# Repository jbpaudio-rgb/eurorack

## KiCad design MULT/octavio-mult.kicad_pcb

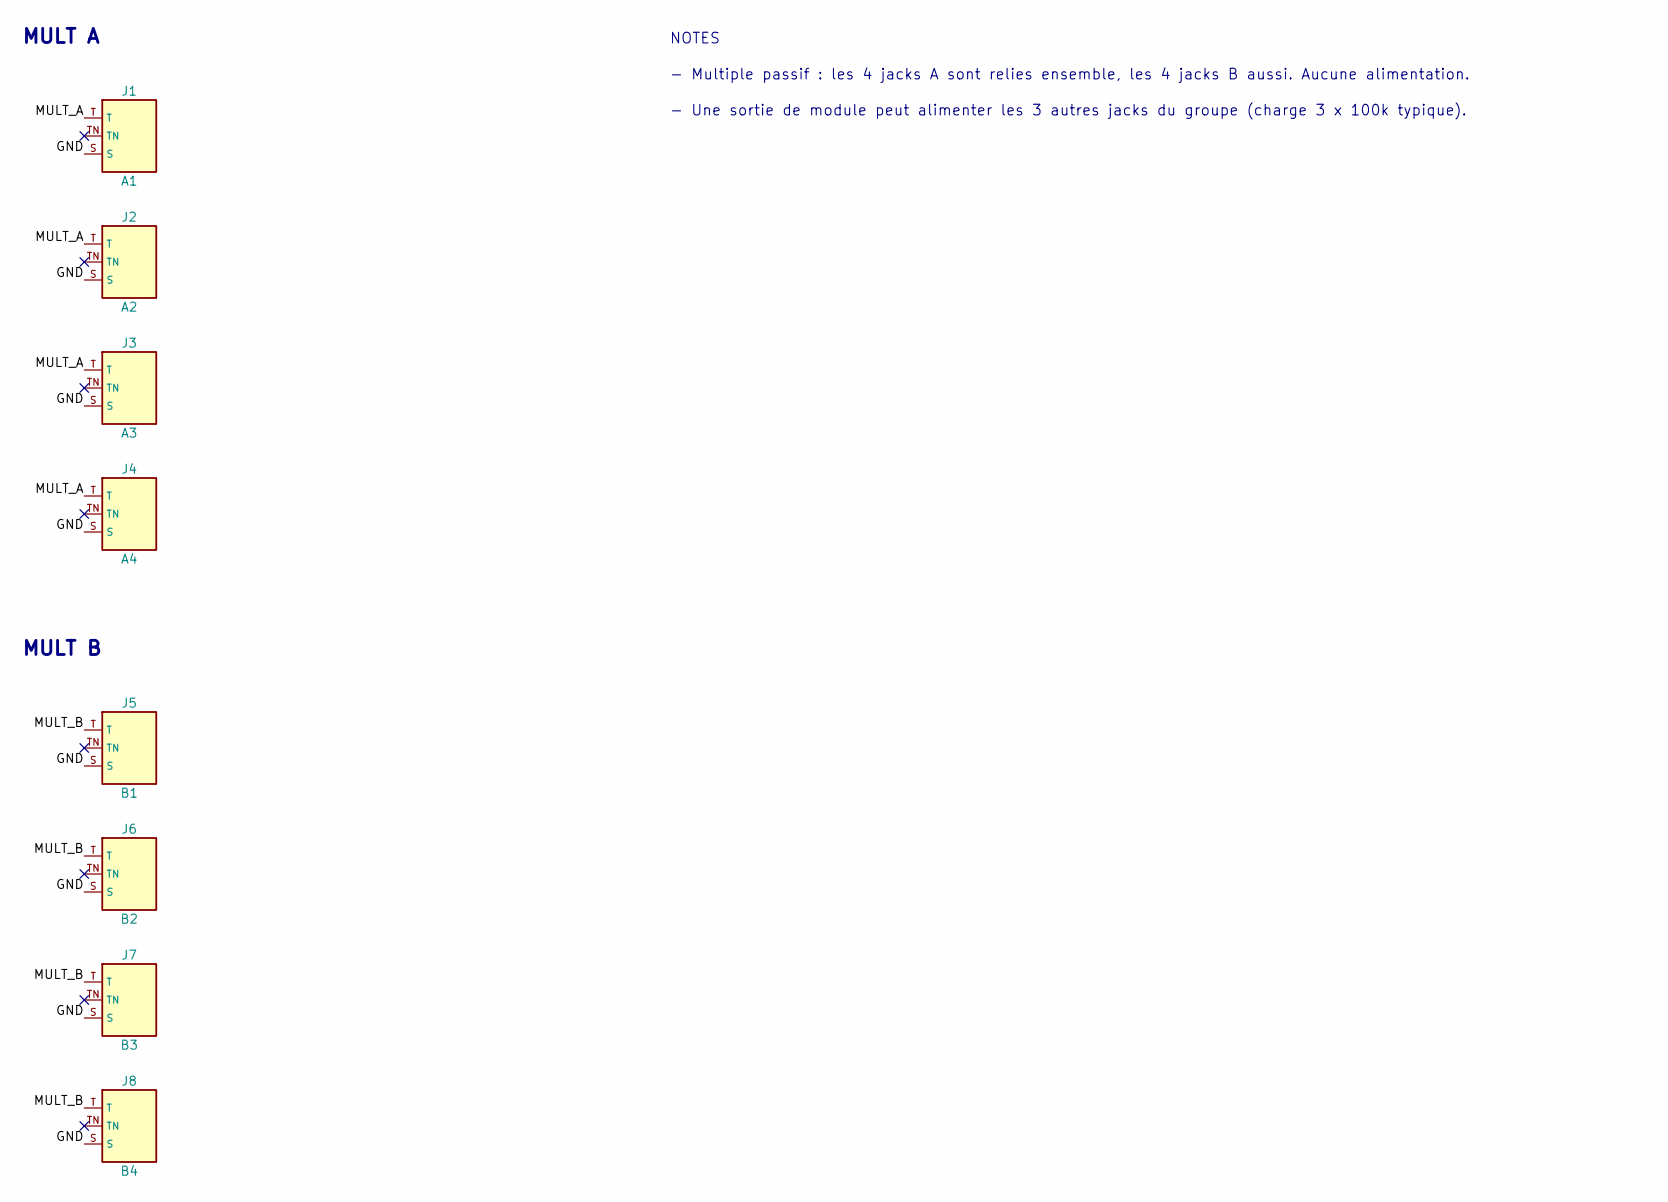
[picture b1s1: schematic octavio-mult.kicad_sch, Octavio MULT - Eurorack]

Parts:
J1: A1; Jack_3.5mm_Thonkiconn_PJ398SM; MPN QingPu WQP-PJ301M-12 (Thonkiconn)
J2: A2; Jack_3.5mm_Thonkiconn_PJ398SM; MPN QingPu WQP-PJ301M-12 (Thonkiconn)
J3: A3; Jack_3.5mm_Thonkiconn_PJ398SM; MPN QingPu WQP-PJ301M-12 (Thonkiconn)
J4: A4; Jack_3.5mm_Thonkiconn_PJ398SM; MPN QingPu WQP-PJ301M-12 (Thonkiconn)
J5: B1; Jack_3.5mm_Thonkiconn_PJ398SM; MPN QingPu WQP-PJ301M-12 (Thonkiconn)
J6: B2; Jack_3.5mm_Thonkiconn_PJ398SM; MPN QingPu WQP-PJ301M-12 (Thonkiconn)
J7: B3; Jack_3.5mm_Thonkiconn_PJ398SM; MPN QingPu WQP-PJ301M-12 (Thonkiconn)
J8: B4; Jack_3.5mm_Thonkiconn_PJ398SM; MPN QingPu WQP-PJ301M-12 (Thonkiconn)

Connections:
GND: J1.S, J2.S, J3.S, J4.S, J5.S, J6.S, J7.S, J8.S
MULT_A: J1.T, J2.T, J3.T, J4.T
MULT_B: J5.T, J6.T, J7.T, J8.T

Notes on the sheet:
MULT A
MULT B
NOTES
- Multiple passif : les 4 jacks A sont relies ensemble, les 4 jacks B aussi. Aucune alimentation.
- Une sortie de module peut alimenter les 3 autres jacks du groupe (charge 3 x 100k typique).

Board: 2 copper layers, 8 parts (0 on the bottom side), 3 nets, no tracks yet.

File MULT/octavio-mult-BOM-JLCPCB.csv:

Comment,Designator,Footprint,LCSC Part #,Notes
A1,J1,Jack_3.5mm_Thonkiconn_PJ398SM,C9900080080,QingPu WQP-PJ301M-12 (Thonkiconn) - THT (wave soldering)
A2,J2,Jack_3.5mm_Thonkiconn_PJ398SM,C9900080080,QingPu WQP-PJ301M-12 (Thonkiconn) - THT (wave soldering)
A3,J3,Jack_3.5mm_Thonkiconn_PJ398SM,C9900080080,QingPu WQP-PJ301M-12 (Thonkiconn) - THT (wave soldering)
A4,J4,Jack_3.5mm_Thonkiconn_PJ398SM,C9900080080,QingPu WQP-PJ301M-12 (Thonkiconn) - THT (wave soldering)
B1,J5,Jack_3.5mm_Thonkiconn_PJ398SM,C9900080080,QingPu WQP-PJ301M-12 (Thonkiconn) - THT (wave soldering)
B2,J6,Jack_3.5mm_Thonkiconn_PJ398SM,C9900080080,QingPu WQP-PJ301M-12 (Thonkiconn) - THT (wave soldering)
B3,J7,Jack_3.5mm_Thonkiconn_PJ398SM,C9900080080,QingPu WQP-PJ301M-12 (Thonkiconn) - THT (wave soldering)
B4,J8,Jack_3.5mm_Thonkiconn_PJ398SM,C9900080080,QingPu WQP-PJ301M-12 (Thonkiconn) - THT (wave soldering)

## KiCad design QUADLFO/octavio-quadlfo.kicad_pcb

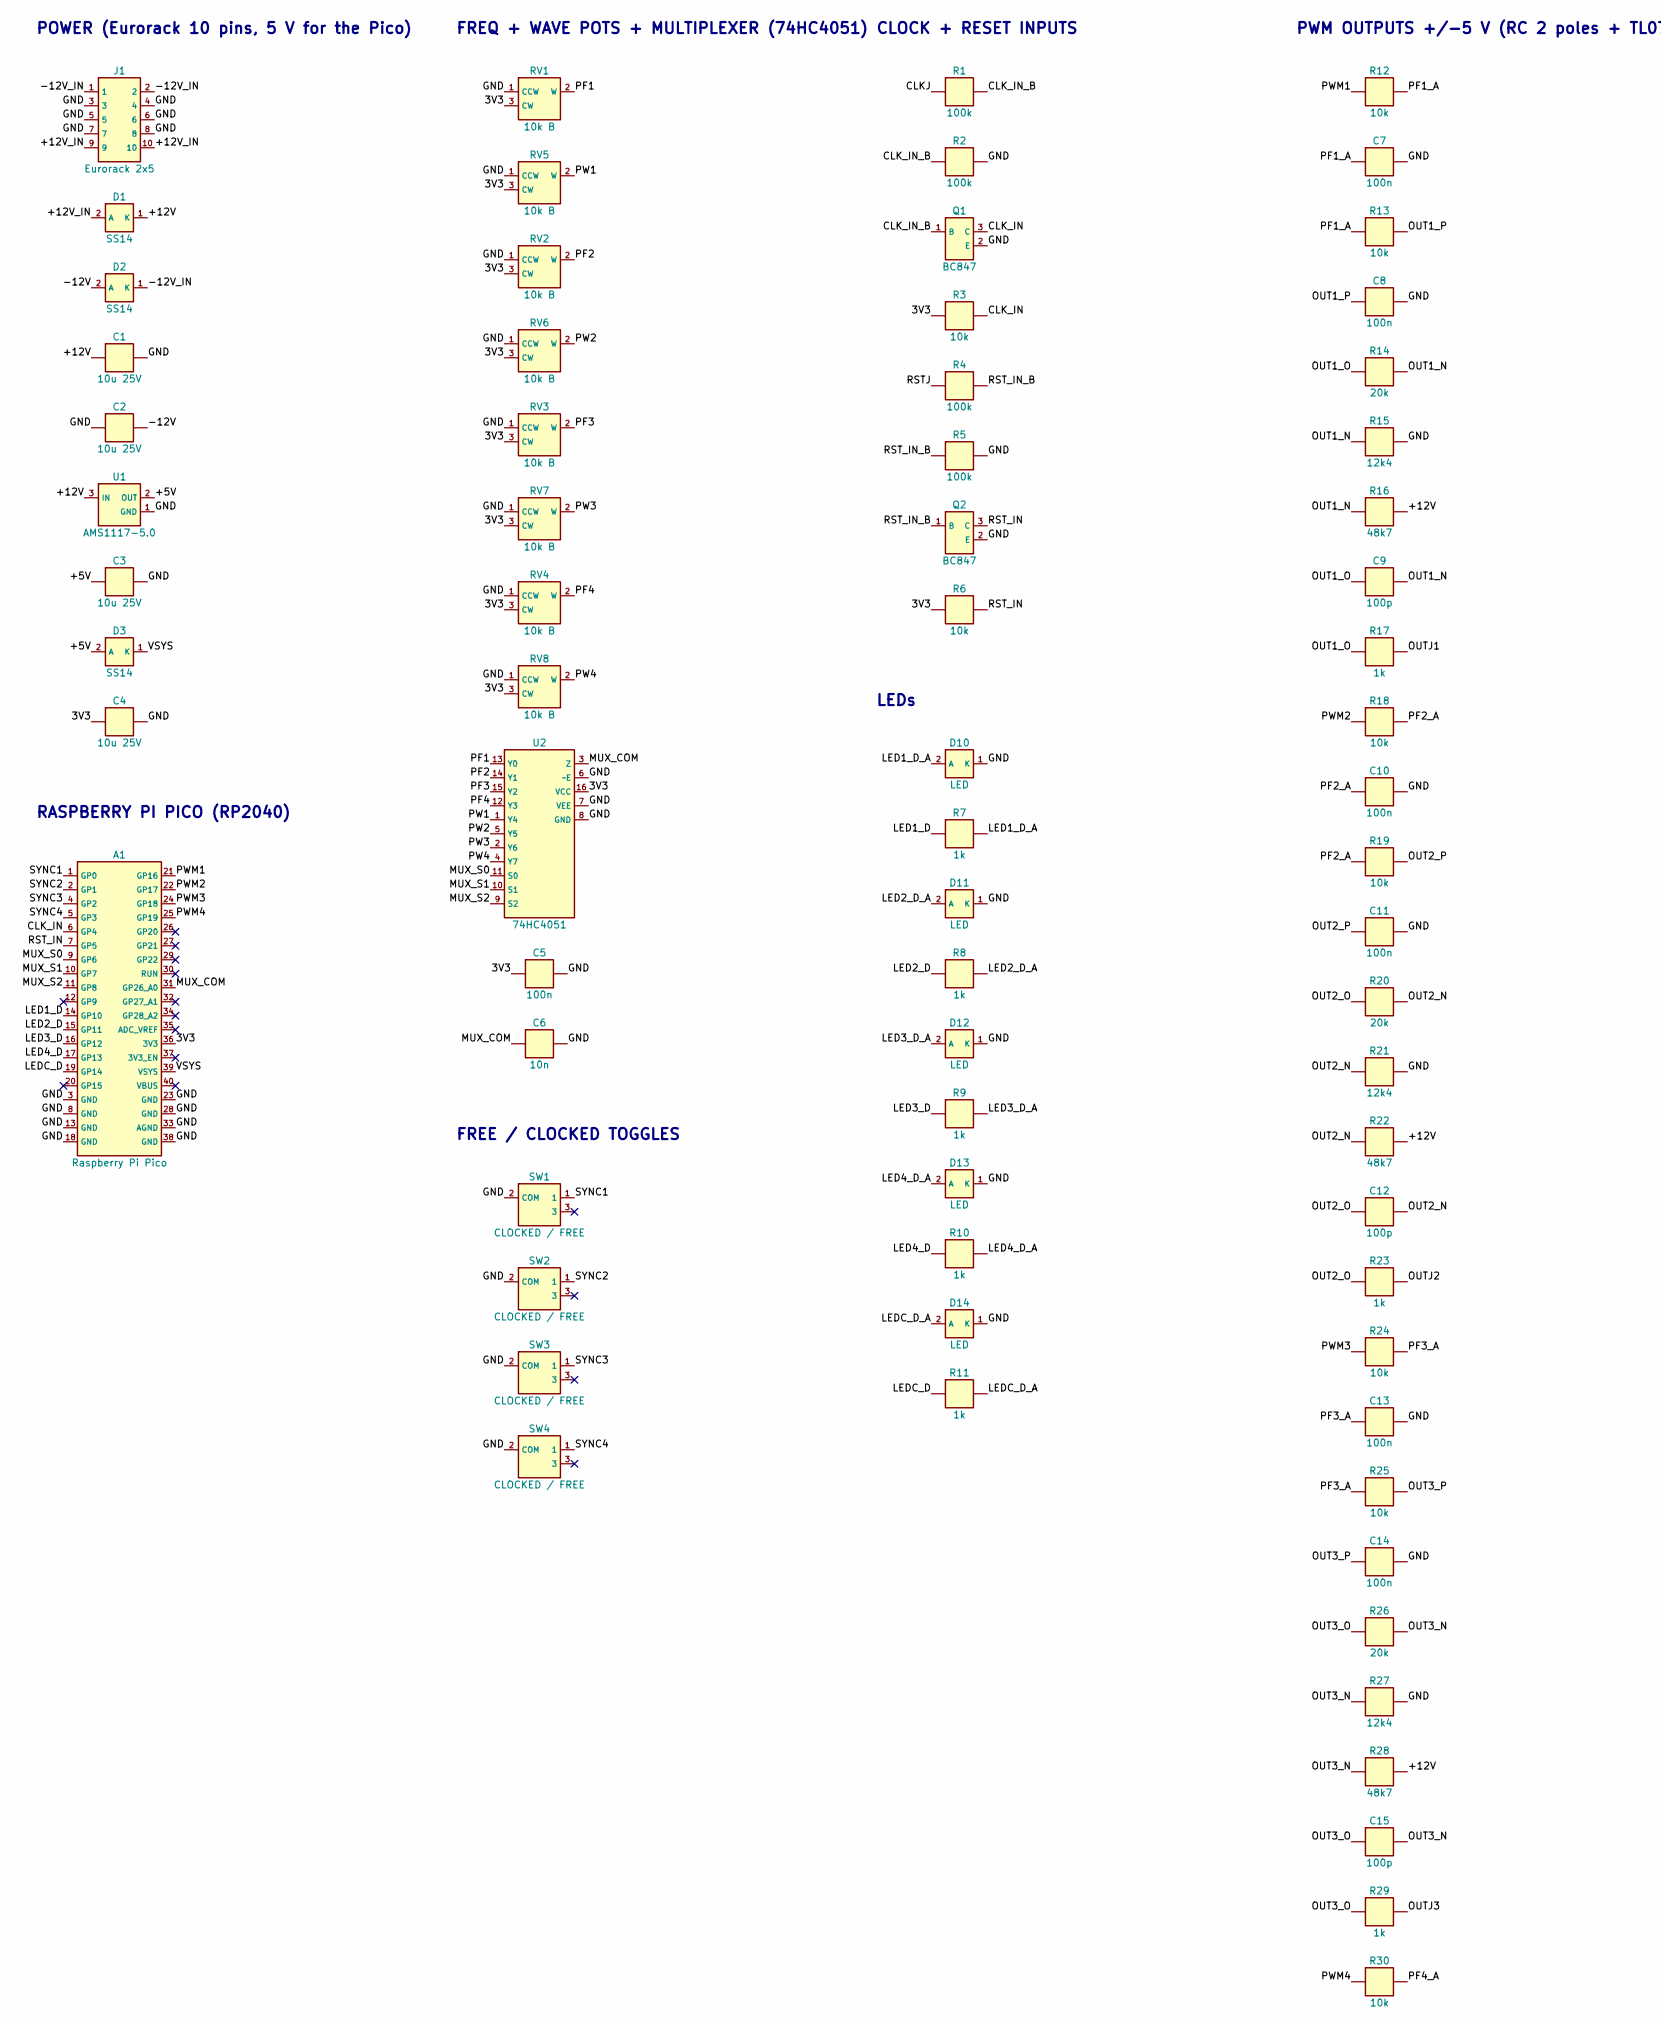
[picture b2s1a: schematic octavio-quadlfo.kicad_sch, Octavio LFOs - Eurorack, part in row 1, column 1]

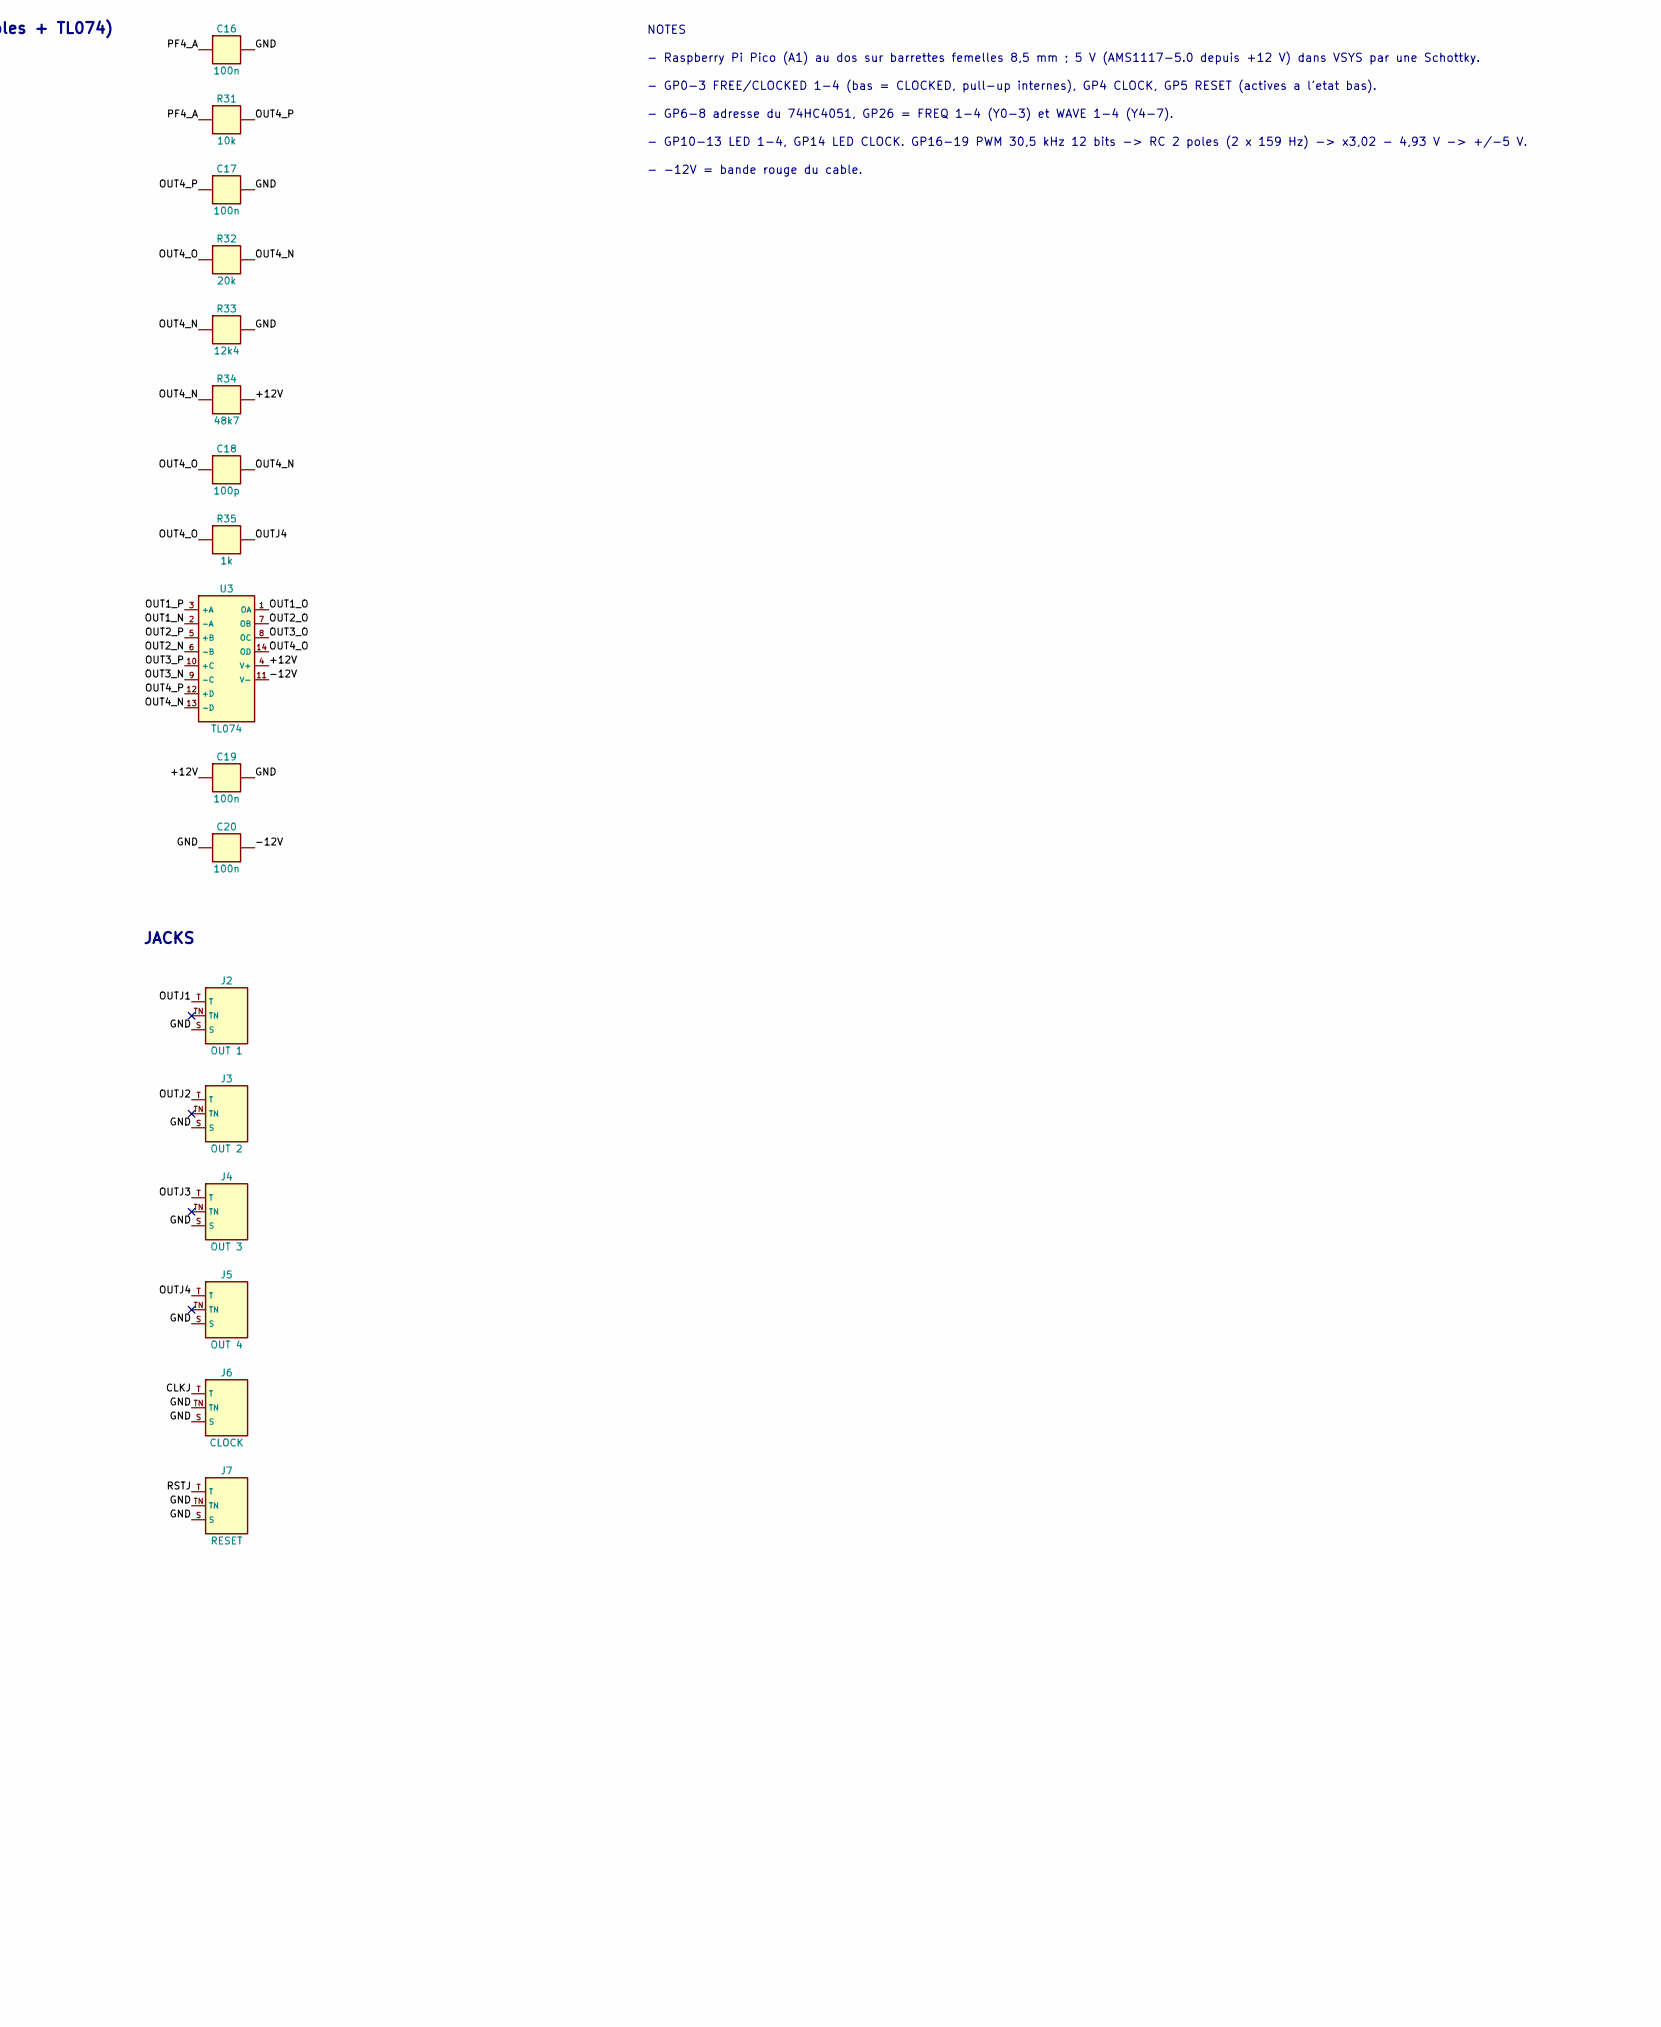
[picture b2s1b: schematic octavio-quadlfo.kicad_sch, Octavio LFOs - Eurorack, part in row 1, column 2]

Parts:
A1: Raspberry Pi Pico; RaspberryPi_Pico_Headers; MPN Raspberry Pi Pico (RP2040) sur 2 barret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
C1, C2, C3: 10u 25V; C_1206_3216Metric; MPN X5R/X7R 1206
C4: 10u 25V; C_1206_3216Metric; MPN X5R/X7R 1206 (3,3 V des potentiomètres 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
C5, C7, C8, C10, C11, C13, C14, C16, C17, C19, C20: 100n; C_0603_1608Metric
C6: 10n; C_0603_1608Metric
C9, C12, C15, C18: 100p; C_0603_1608Metric
D1, D2: SS14; D_SMA; MPN SS14 (40 V 1 A Schottky)
D3: SS14; D_SMA; MPN SS14 (Schottky : USB et rack peuvent êt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
D10, D11, D12, D13: LED; LED_D3.0mm; MPN LED 3 mm rouge (suit le LFO, PWM)
D14: LED; LED_D3.0mm; MPN LED 3 mm ambre (CLOCK)
J1: Eurorack 2x5; IDC-Header_2x05_P2.54mm_Vertical; MPN Shrouded header 2x5 2.54 mm
J2: OUT 1; Jack_3.5mm_Thonkiconn_PJ398SM; MPN QingPu WQP-PJ301M-12 (Thonkiconn)
J3: OUT 2; Jack_3.5mm_Thonkiconn_PJ398SM; MPN QingPu WQP-PJ301M-12 (Thonkiconn)
J4: OUT 3; Jack_3.5mm_Thonkiconn_PJ398SM; MPN QingPu WQP-PJ301M-12 (Thonkiconn)
J5: OUT 4; Jack_3.5mm_Thonkiconn_PJ398SM; MPN QingPu WQP-PJ301M-12 (Thonkiconn)
J6: CLOCK; Jack_3.5mm_Thonkiconn_PJ398SM; MPN QingPu WQP-PJ301M-12 (Thonkiconn)
J7: RESET; Jack_3.5mm_Thonkiconn_PJ398SM; MPN QingPu WQP-PJ301M-12 (Thonkiconn)
Q1, Q2: BC847; SOT-23; MPN BC847C
R1, R2, R4, R5: 100k; R_0603_1608Metric
R3, R6, R12, R13, R18, R19, R24, R25, R30, R31: 10k; R_0603_1608Metric
R7, R8, R9, R10, R11, R17, R23, R29, R35: 1k; R_0603_1608Metric
R14, R20, R26, R32: 20k; R_0603_1608Metric
R15, R21, R27, R33: 12k4; R_0603_1608Metric
R16, R22, R28, R34: 48k7; R_0603_1608Metric
RV1, RV2, RV3, RV4, RV5, RV6, RV7, RV8: 10k B; Pot_Alpha_9mm_Vertical; MPN POT-R09V-10K (9 mm vertical, B10k)
SW1, SW2, SW3, SW4: CLOCKED / FREE; Toggle_SPDT_Dailywell_2MS1; MPN Dailywell 2MS1T1B1M2QES (SPDT ON-ON, le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
U1: AMS1117-5.0; SOT-223-3_TabPin2; MPN AMS1117-5.0 (C6187)
U2: 74HC4051; SOIC-16_3.9x9.9mm_P1.27mm; MPN 74HC4051D
U3: TL074; SOIC-14_3.9x8.7mm_P1.27mm; MPN TL074CDR

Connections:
3V3: A1.36 (3V3), C4.1, C5.1, R3.1, R6.1, RV1.3 (CW), RV2.3 (CW), RV3.3 (CW), RV4.3 (CW), RV5.3 (CW), RV6.3 (CW), RV7.3 (CW), RV8.3 (CW), U2.16 (VCC)
+5V: C3.1, D3.2 (A), U1.2 (OUT)
+12V: C1.1, C19.1, D1.1 (K), R16.2, R22.2, R28.2, R34.2, U1.3 (IN), U3.4 (V+)
+12V_IN: D1.2 (A), J1.9, J1.10
-12V: C2.2, C20.2, D2.2 (A), U3.11 (V-)
-12V_IN: D2.1 (K), J1.1, J1.2
CLKJ: J6.T, R1.1
CLK_IN: A1.6 (GP4), Q1.3 (C), R3.2
CLK_IN_B: Q1.1 (B), R1.2, R2.1
GND: A1.3 (GND), A1.8 (GND), A1.13 (GND), A1.18 (GND), A1.23 (GND), A1.28 (GND), A1.33 (AGND), A1.38 (GND), C1.2, C2.1, C3.2, C4.2, C5.2, C6.2, C7.2, C8.2, C10.2, C11.2, C13.2, C14.2, C16.2, C17.2, C19.2, C20.1, D10.1 (K), D11.1 (K), D12.1 (K), D13.1 (K), D14.1 (K), J1.3, J1.4, J1.5, J1.6, J1.7, J1.8, J2.S, J3.S, J4.S, J5.S, J6.S, J6.TN, J7.S, J7.TN, Q1.2 (E), Q2.2 (E), R2.2, R5.2, R15.2, R21.2, R27.2, R33.2, RV1.1 (CCW), RV2.1 (CCW), RV3.1 (CCW), RV4.1 (CCW), RV5.1 (CCW), RV6.1 (CCW), RV7.1 (CCW), RV8.1 (CCW), SW1.2 (COM), SW2.2 (COM), SW3.2 (COM), SW4.2 (COM), U1.1 (GND), U2.6 (~E), U2.7 (VEE), U2.8 (GND)
LED1_D: A1.14 (GP10), R7.1
LED1_D_A: D10.2 (A), R7.2
LED2_D: A1.15 (GP11), R8.1
LED2_D_A: D11.2 (A), R8.2
LED3_D: A1.16 (GP12), R9.1
LED3_D_A: D12.2 (A), R9.2
LED4_D: A1.17 (GP13), R10.1
LED4_D_A: D13.2 (A), R10.2
LEDC_D: A1.19 (GP14), R11.1
LEDC_D_A: D14.2 (A), R11.2
MUX_COM: A1.31 (GP26_A0), C6.1, U2.3 (Z)
MUX_S0: A1.9 (GP6), U2.11 (S0)
MUX_S1: A1.10 (GP7), U2.10 (S1)
MUX_S2: A1.11 (GP8), U2.9 (S2)
OUT1_N: C9.2, R14.2, R15.1, R16.1, U3.2 (-A)
OUT1_O: C9.1, R14.1, R17.1, U3.1 (OA)
OUT1_P: C8.1, R13.2, U3.3 (+A)
OUT2_N: C12.2, R20.2, R21.1, R22.1, U3.6 (-B)
OUT2_O: C12.1, R20.1, R23.1, U3.7 (OB)
OUT2_P: C11.1, R19.2, U3.5 (+B)
OUT3_N: C15.2, R26.2, R27.1, R28.1, U3.9 (-C)
OUT3_O: C15.1, R26.1, R29.1, U3.8 (OC)
OUT3_P: C14.1, R25.2, U3.10 (+C)
OUT4_N: C18.2, R32.2, R33.1, R34.1, U3.13 (-D)
OUT4_O: C18.1, R32.1, R35.1, U3.14 (OD)
OUT4_P: C17.1, R31.2, U3.12 (+D)
OUTJ1: J2.T, R17.2
OUTJ2: J3.T, R23.2
OUTJ3: J4.T, R29.2
OUTJ4: J5.T, R35.2
PF1: RV1.2 (W), U2.13 (Y0)
PF1_A: C7.1, R12.2, R13.1
PF2: RV2.2 (W), U2.14 (Y1)
PF2_A: C10.1, R18.2, R19.1
PF3: RV3.2 (W), U2.15 (Y2)
PF3_A: C13.1, R24.2, R25.1
PF4: RV4.2 (W), U2.12 (Y3)
PF4_A: C16.1, R30.2, R31.1
PW1: RV5.2 (W), U2.1 (Y4)
PW2: RV6.2 (W), U2.5 (Y5)
PW3: RV7.2 (W), U2.2 (Y6)
PW4: RV8.2 (W), U2.4 (Y7)
PWM1: A1.21 (GP16), R12.1
PWM2: A1.22 (GP17), R18.1
PWM3: A1.24 (GP18), R24.1
PWM4: A1.25 (GP19), R30.1
RSTJ: J7.T, R4.1
RST_IN: A1.7 (GP5), Q2.3 (C), R6.2
RST_IN_B: Q2.1 (B), R4.2, R5.1
SYNC1: A1.1 (GP0), SW1.1
SYNC2: A1.2 (GP1), SW2.1
SYNC3: A1.4 (GP2), SW3.1
SYNC4: A1.5 (GP3), SW4.1
VSYS: A1.39 (VSYS), D3.1 (K)

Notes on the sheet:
POWER (Eurorack 10 pins, 5 V for the Pico)
RASPBERRY PI PICO (RP2040)
FREQ + WAVE POTS + MULTIPLEXER (74HC4051)
FREE / CLOCKED TOGGLES
CLOCK + RESET INPUTS
LEDs
PWM OUTPUTS +/-5 V (RC 2 poles + TL074)
JACKS
NOTES
- Raspberry Pi Pico (A1) au dos sur barrettes femelles 8,5 mm ; 5 V (AMS1117-5.0 depuis +12 V) dans VSYS par une Schottky.
- GP0-3 FREE/CLOCKED 1-4 (bas = CLOCKED, pull-up internes), GP4 CLOCK, GP5 RESET (actives a l'etat bas).
- GP6-8 adresse du 74HC4051, GP26 = FREQ 1-4 (Y0-3) et WAVE 1-4 (Y4-7).
- GP10-13 LED 1-4, GP14 LED CLOCK. GP16-19 PWM 30,5 kHz 12 bits -> RC 2 poles (2 x 159 Hz) -> x3,02 - 4,93 V -> +/-5 V.
- -12V = bande rouge du cable.

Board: 2 copper layers, 88 parts (65 on the bottom side), 64 nets, no tracks yet.

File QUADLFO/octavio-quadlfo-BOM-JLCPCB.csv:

Comment,Designator,Footprint,LCSC Part #,Notes
Raspberry Pi Pico,A1,RaspberryPi_Pico_Headers,,"Raspberry Pi Pico (RP2040) sur 2 barrettes femelles 1x20 2,54 mm, 8,5 mm (soudées à la main) - THT (wave soldering) - laisser JLC choisir (Basic de preference)"
10u 25V X5R/X7R 1206,"C1,C2,C3",C_1206_3216Metric,,X5R/X7R 1206 - SMT bottom - laisser JLC choisir (Basic de preference)
10u 25V X5R/X7R 1206,C4,C_1206_3216Metric,,"X5R/X7R 1206 (3,3 V des potentiomètres et DAC) - SMT bottom - laisser JLC choisir (Basic de preference)"
100n,"C5,C7,C8,C10,C11,C13,C14,C16,C17,C19,C20",C_0603_1608Metric,,SMT bottom - laisser JLC choisir (Basic de preference)
10n,C6,C_0603_1608Metric,,SMT bottom - laisser JLC choisir (Basic de preference)
100p,"C9,C12,C15,C18",C_0603_1608Metric,,SMT bottom - laisser JLC choisir (Basic de preference)
SS14,"D1,D2",D_SMA,,SS14 (40 V 1 A Schottky) - SMT bottom - laisser JLC choisir (Basic de preference)
LED,"D10,D11,D12,D13",LED_D3.0mm,,"LED 3 mm rouge (suit le LFO, PWM) - THT (wave soldering) - laisser JLC choisir (Basic de preference)"
LED,D14,LED_D3.0mm,,LED 3 mm ambre (CLOCK) - THT (wave soldering) - laisser JLC choisir (Basic de preference)
SS14,D3,D_SMA,,SS14 (Schottky : USB et rack peuvent être branchés ensemble) - SMT bottom - laisser JLC choisir (Basic de preference)
Eurorack 2x5,J1,IDC-Header_2x05_P2.54mm_Vertical,,Shrouded header 2x5 2.54 mm - THT (wave soldering) - laisser JLC choisir (Basic de preference)
OUT 1,J2,Jack_3.5mm_Thonkiconn_PJ398SM,C9900080080,QingPu WQP-PJ301M-12 (Thonkiconn) - THT (wave soldering)
OUT 2,J3,Jack_3.5mm_Thonkiconn_PJ398SM,C9900080080,QingPu WQP-PJ301M-12 (Thonkiconn) - THT (wave soldering)
OUT 3,J4,Jack_3.5mm_Thonkiconn_PJ398SM,C9900080080,QingPu WQP-PJ301M-12 (Thonkiconn) - THT (wave soldering)
OUT 4,J5,Jack_3.5mm_Thonkiconn_PJ398SM,C9900080080,QingPu WQP-PJ301M-12 (Thonkiconn) - THT (wave soldering)
CLOCK,J6,Jack_3.5mm_Thonkiconn_PJ398SM,C9900080080,QingPu WQP-PJ301M-12 (Thonkiconn) - THT (wave soldering)
RESET,J7,Jack_3.5mm_Thonkiconn_PJ398SM,C9900080080,QingPu WQP-PJ301M-12 (Thonkiconn) - THT (wave soldering)
BC847C,"Q1,Q2",SOT-23,,BC847C - SMT bottom - laisser JLC choisir (Basic de preference)
100k 1% 0805,"R1,R2,R4,R5",R_0603_1608Metric,,SMT bottom - laisser JLC choisir (Basic de preference)
20k 1% 0805,"R14,R20,R26,R32",R_0603_1608Metric,,SMT bottom - laisser JLC choisir (Basic de preference)
12k4 1% 0805,"R15,R21,R27,R33",R_0603_1608Metric,,SMT bottom - laisser JLC choisir (Basic de preference)
48k7 1% 0805,"R16,R22,R28,R34",R_0603_1608Metric,,SMT bottom - laisser JLC choisir (Basic de preference)
10k 1% 0805,"R3,R6,R12,R13,R18,R19,R24,R25,R30,R31",R_0603_1608Metric,,SMT bottom - laisser JLC choisir (Basic de preference)
1k 1% 0805,"R7,R8,R9,R10,R11,R17,R23,R29,R35",R_0603_1608Metric,,SMT bottom - laisser JLC choisir (Basic de preference)
10k B,"RV1,RV5,RV2,RV6,RV3,RV7,RV4,RV8",Pot_Alpha_9mm_Vertical,,"POT-R09V-10K (9 mm vertical, B10k) - THT (wave soldering) - laisser JLC choisir (Basic de preference)"
CLOCKED / FREE,"SW1,SW2,SW3,SW4",Toggle_SPDT_Dailywell_2MS1,,"Dailywell 2MS1T1B1M2QES (SPDT ON-ON, le moins cher) - THT (wave soldering) - laisser JLC choisir (Basic de preference)"
AMS1117-5.0,U1,SOT-223-3_TabPin2,,AMS1117-5.0 (C6187) - SMT bottom - laisser JLC choisir (Basic de preference)
74HC4051D,U2,SOIC-16_3.9x9.9mm_P1.27mm,,74HC4051D - SMT bottom - laisser JLC choisir (Basic de preference)
TL074CDR,U3,SOIC-14_3.9x8.7mm_P1.27mm,C12594,TL074CDR - SMT bottom
